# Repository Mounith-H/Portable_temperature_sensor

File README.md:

# Portable Temperature Sensor

<div align="center">
  
</div>

## Overview

The Portable Temperature Sensor is a wireless IoT temperature monitoring device based on the ESP8266 NodeMCU platform. It uses a MAX6675 thermocouple interface to measure temperatures up to 1024°C with high precision, making it suitable for industrial monitoring, cooking, 3D printing, and scientific applications.

### Key Features

- **High-Temperature Measurement:** Uses the MAX6675 thermocouple for accurate measurements up to 1024°C
- **Wireless Connectivity:** Built-in WiFi for remote monitoring and control
- **MQTT Support:** Integrates with home automation systems and custom dashboards
- **Alarm System:** Configurable temperature thresholds with buzzer alerts
- **Interrupt Output:** Provides digital signal output when temperature exceeds thresholds
- **Custom PCB Design:** Optimized layout with full KiCad design files
- **Serial Communication:** Both USB and software serial interfaces for flexible integration

## Hardware Components

- **NodeMCU ESP8266** - Main controller with WiFi capability
- **MAX6675 Module** - K-type thermocouple interface
- **K-Type Thermocouple** - High-temperature sensing element
- **Buzzer** - For audible alerts
- **Passive Components** - Resistors, capacitors for circuit stability

## Pin Connections

| Pin Numbers | Pin Names | Pin Function | Other    | Connection   |
|-------------|-----------|-------------|----------|--------------|
| ADC0        | A0        | Analog Input | X        | X            |
| GPIO16      | D0        | WAKE        | X        | SEN-CS       |
| GPIO5       | D1        | SCL         | X        | OLED/ SCL    |
| GPIO4       | D2        | SDA         | X        | OLED/ SDA    |
| GPIO0       | D3        | FLASH       | Pull-up  | BUZZER       |
| GPIO2       | D4        | TXD1/LED    | Pull-up  | INTERRUPT    |
| GPIO14      | D5        | SCLK        | X        | SEN-SCK      |
| GPIO12      | D6        | MISO        | X        | SEN-SO       |
| GPIO13      | D7        | MOSI/RXD2   | X        | UART-RX      |
| GPIO15      | D8        | CS/TXD2     | Pull-down| UART-TX      |
| GPIO3       | RX        | RXD0        | X        | X            |
| GPIO1       | TX        | TXD0        | X        | X            |
| RST         | RST       | Reset       | Pull-up  | X            |

## Software Setup

### Prerequisites

- [PlatformIO](https://platformio.org/) (recommended) or Arduino IDE
- Required libraries:
  - PubSubClient for MQTT
  - EspSoftwareSerial for additional serial ports
  - Adafruit MAX6675 for thermocouple interface
  - GyverOLED for display support (optional - will be implemented separately)

### Installation

1. Clone this repository:
   ```
   git clone https://github.com/MOUNITH-H/Portable_temperature_sensor.git
   ```

2. Open the project in PlatformIO or Arduino IDE:
   - For PlatformIO: Open the `Portable_temperature_sensor` folder
   - For Arduino IDE: Open `src/main.cpp` as your sketch

3. Configure WiFi and MQTT settings:
   - Edit the connection parameters in `main.cpp`

4. Build and upload to your NodeMCU

## PCB Design

The project includes a custom PCB design created with KiCad. The design files are in the `pcb` folder:

- Full schematic in `pcb.kicad_sch`
- PCB layout in `pcb.kicad_pcb`
- Interactive BOM available in `pcb/bom/ibom.html`

## Usage

1. Power the device using USB or a 5V power source
2. The device will automatically connect to the configured WiFi network
3. Temperature data is published to the MQTT topic `portable_temp_sensor/temperature`
4. The buzzer will sound if the temperature exceeds the configured threshold
5. Configure alarm settings via the MQTT topic `portable_temp_sensor/settings`

## MQTT Topics

| Topic | Description | Message Format |
|-------|-------------|----------------|
| `portable_temp_sensor/temperature` | Current temperature readings | `{"temp": 25.4, "timestamp": 1620123456}` |
| `portable_temp_sensor/settings` | Device configuration | `{"threshold": 80, "buzzer_enabled": true}` |
| `portable_temp_sensor/status` | Device status information | `{"uptime": 3600, "wifi_strength": -67}` |

## Troubleshooting

- **No temperature readings:** Check thermocouple connections
- **Cannot connect to WiFi:** Verify credentials in the code
- **MQTT connection issues:** Confirm server address and port settings
- **Erratic readings:** Check for interference with thermocouple wires

## TODO
- [ ] Convert to FreeRTOS

## Contributing

Contributions are welcome! Please feel free to submit a Pull Request.

## License

This project is licensed under the MIT License - see the [LICENSE](LICENSE) file for details.

## Author

- **MOUNITH H** - *Initial work*

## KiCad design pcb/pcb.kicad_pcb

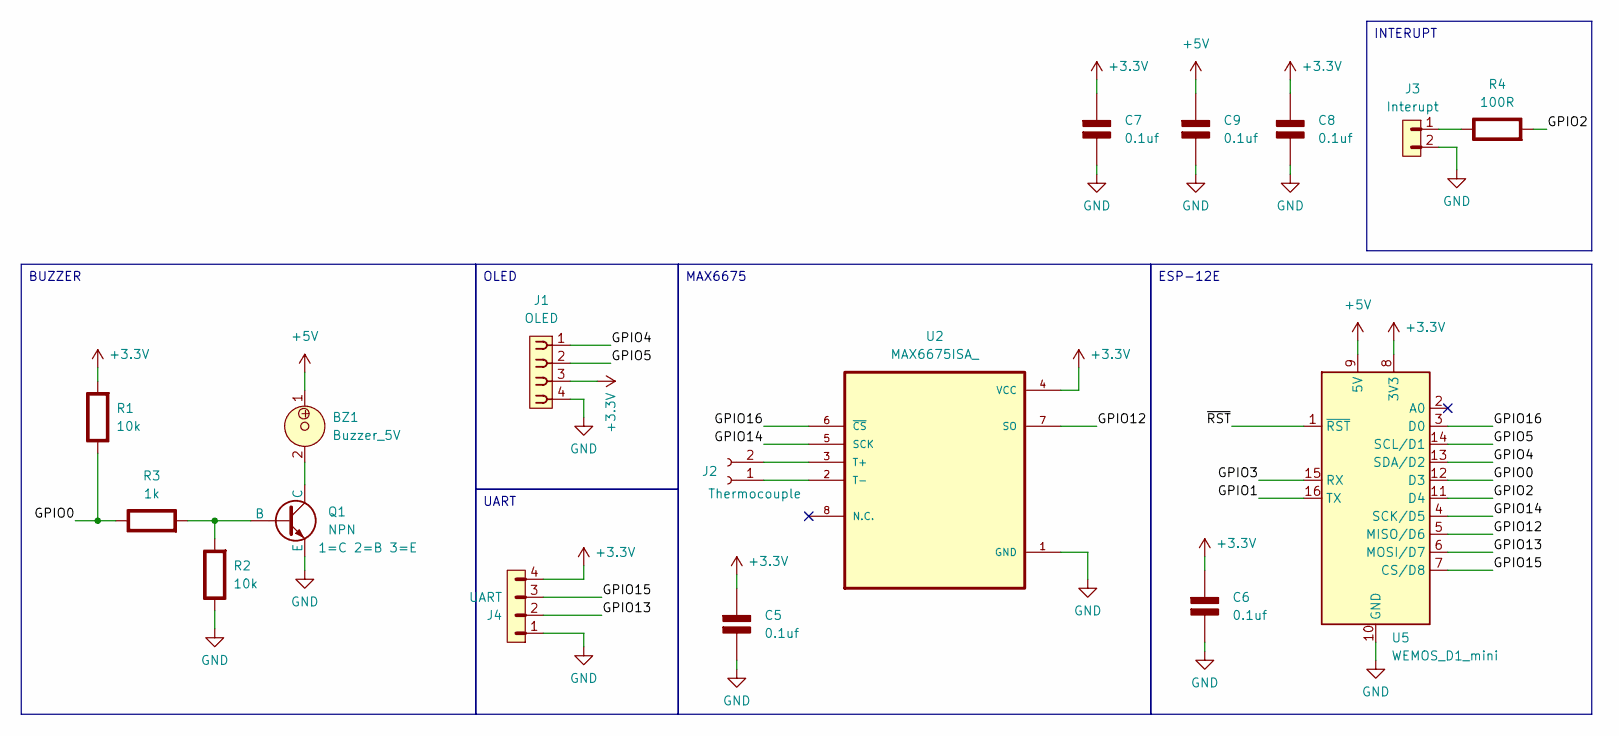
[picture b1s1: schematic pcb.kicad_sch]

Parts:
BZ1: Buzzer_5V; Buzzer_12x9.5RM7.6
C5, C6, C7, C8, C9: 0.1uf; C_1206_3216Metric_Pad1.33x1.80mm_HandSolder; Rating V
J1: OLED; PinSocket_1x04_P2.54mm_Vertical
J2: Thermocouple; TerminalBlock_MetzConnect_Type175_RT02702HBLC_1x02_P7.50mm_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
J3: Interupt; PinHeader_1x02_P2.54mm_Vertical
J4: UART; PinHeader_1x04_P2.54mm_Vertical
Q1: NPN; SOT-23-3
R1: 10k; R_Axial_DIN0207_L6.3mm_D2.5mm_P10.16mm_Horizontal; Rating W
R2: 10k; R_1206_3216Metric_Pad1.30x1.75mm_HandSolder; Rating W
R3: 1k; R_1206_3216Metric_Pad1.30x1.75mm_HandSolder; Rating W
R4: 100R; R_Axial_DIN0207_L6.3mm_D2.5mm_P10.16mm_Horizontal; Rating W
U2: MAX6675ISA_; MAX6675ISA__SOIC127P600X175-8N
U5: WEMOS_D1_mini; WEMOS_D1_mini_light

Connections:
+3.3V: C5.1 (+), C6.1 (+), C7.1 (+), C8.1 (+), J1.3, J4.4, R1.2 (-), U2.4 (VCC), U5.8 (3V3)
+5V: BZ1.1, C9.1 (+), U5.9 (5V)
/GPIO0: R1.1 (+), R3.1 (+), U5.12 (D3)
/GPIO1: U5.16 (TX)
/GPIO2: R4.2 (-), U5.11 (D4)
/GPIO3: U5.15 (RX)
/GPIO4: J1.1, U5.13 (SDA/D2)
/GPIO5: J1.2, U5.14 (SCL/D1)
/GPIO12: U2.7 (SO), U5.5 (MISO/D6)
/GPIO13: J4.2, U5.6 (MOSI/D7)
/GPIO14: U2.5 (SCK), U5.4 (SCK/D5)
/GPIO15: J4.3, U5.7 (CS/D8)
/GPIO16: U2.6 (~CS), U5.3 (D0)
/~RST: U5.1 (~RST)
GND: C5.2 (-), C6.2 (-), C7.2 (-), C8.2 (-), C9.2 (-), J1.4, J3.2, J4.1, Q1.3 (E), R2.1 (+), U2.1 (GND), U5.10 (GND)
unnamed: J2.1, U2.2 (T-)
unnamed: J2.2, U2.3 (T+)
unnamed: Q1.2 (B), R2.2 (-), R3.2 (-)
unnamed: BZ1.2, Q1.1 (C)
unnamed: J3.1, R4.1 (+)

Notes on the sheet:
UART
BUZZER
MAX6675
INTERUPT
ESP-12E
OLED

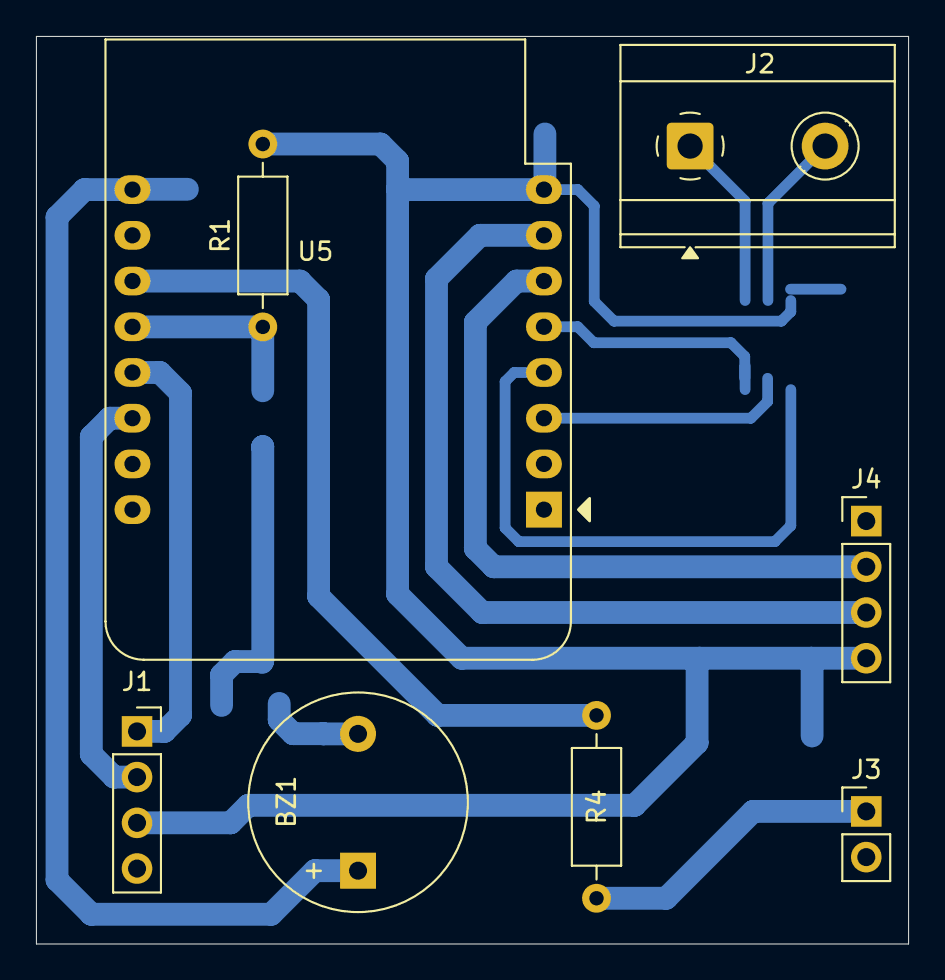
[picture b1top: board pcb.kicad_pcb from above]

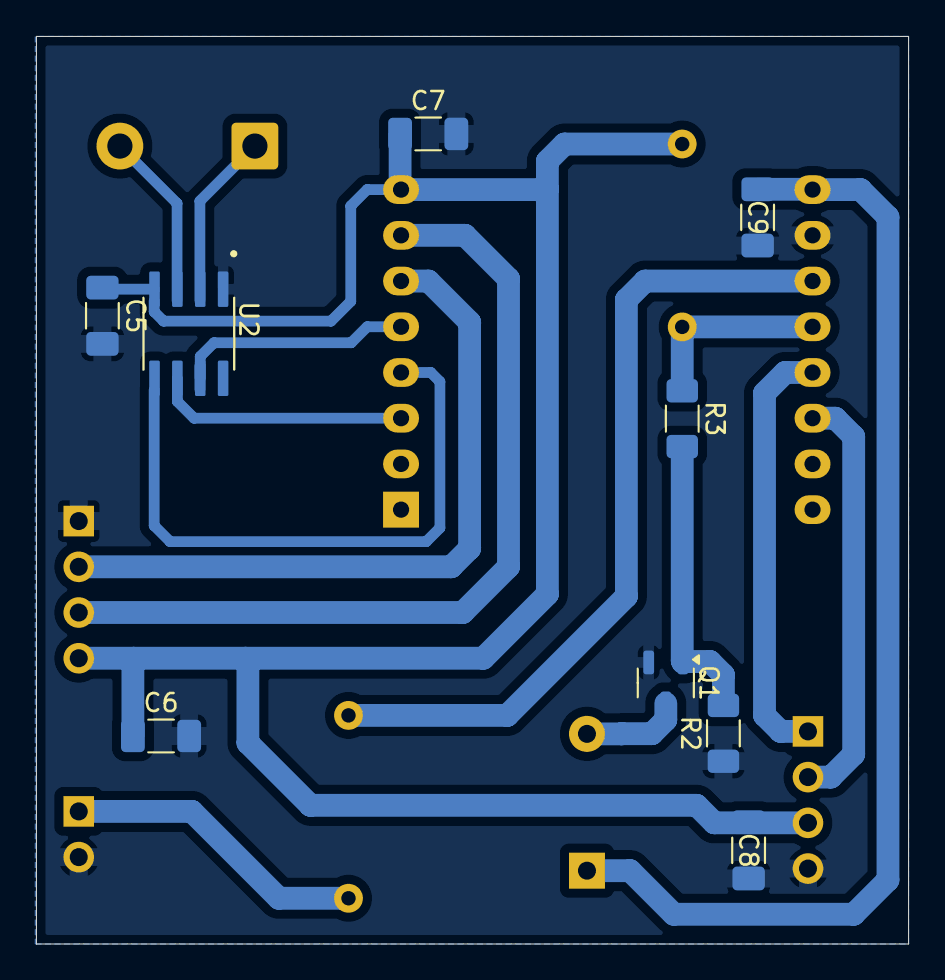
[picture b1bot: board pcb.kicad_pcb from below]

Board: 2 copper layers, 48.5 x 50.4 mm, 17 parts (9 on the bottom side), 17 nets.

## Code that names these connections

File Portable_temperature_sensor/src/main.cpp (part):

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HARDWARE CONNECTIONS:

MAX6675 Thermocouple:
- SO  → GPIO12 (D6)  // Data from sensor
- CS  → GPIO16 (D0)  // Chip select
- SCK → GPIO14 (D5)  // Clock signal

OLED Display (I2C):
- SDA → GPIO4  (D2)
- SCL → GPIO5  (D1)

Peripherals:
- Buzzer   → GPIO0  (D3)  // Alarm when temperature exceeds threshold
- Interrupt → GPIO2  (D4)  // External trigger signal

Communication:
- Software Serial: RX→GPIO13 (D7), TX→GPIO15 (D8)  // For external comms
- Hardware Serial: USB port (115200 baud)          // For debugging

Power Requirements:
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*/

// External communication port (separate from debug serial)
const int SOFT_RX = 13;  // GPIO13 (D7)
const int SOFT_TX = 15;  // GPIO15 (D8)
SoftwareSerial softSerial(SOFT_RX, SOFT_TX);

// MAX6675 thermocouple interface pins
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PubSubClient mqttClient(espClient);
NetworkManager networkManager(ssid, password);

// OLED display definitions (I2C PCB: SDA=GPIO4, SCL=GPIO5)
#define SCREEN_WIDTH 128
#define SCREEN_HEIGHT 32
#define OLED_WHITE 1  // Color constant for drawing in white
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
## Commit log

2025-05-10 Edit README.md
2025-05-10 edited Portable_temperature_sensor README
2025-05-10 fixed network status indicators in oled
2025-05-10 Implemented splash screen
2025-05-10 updated changes in pcb
2025-05-11 added battery functionality, updated pcb

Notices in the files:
README.md:
License: MIT
